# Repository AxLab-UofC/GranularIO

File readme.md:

# Granular IO
This repo contains the GUI, Arduino code, mechanical and electrical design files of the Granular IO project.

## Publication

Chi Wang, Clara Cui, Alan Pham, Justice T Andersen, Tucker Rae-Grant, and Ken Nakagaki. **Granular I/O: Enabling Bi-directional Malleable Interaction for Actuated TUIs with Magnetic Particles.** *ACM Symposium on User Interface Software and Technology (UIST 2026).* [DOI: 10.1145/3830398.3830589](https://doi.org/10.1145/3830398.3830589).

[Project Website](https://www.axlab.cs.uchicago.edu/projects/granular-io) | [Paper PDF](https://www.axlab.cs.uchicago.edu/_files/ugd/bef049_0de81f3c0d4b4951962cf3efb3ace36e.pdf) | [DOI](https://doi.org/10.1145/3830398.3830589) | [Video](https://youtu.be/jblO1pQyjmk)

## Repository structure

```text
GranularIO/
├── ArduinoCode/
│   ├── EM/                         # Firmware for the EM platform
│   └── LAPM/                       # Firmware for the LAPM platform
├── GUI/
│   └── GranularIO/                 # Graphical user interface
├── Hardware/
│   ├── EM/                         # Electromagnet array fabrication files
│   │   ├── 1_EM_Cover.stl
│   │   ├── 2_EM_Hub.stl
│   │   ├── 3_MetalDisk.step
│   │   ├── EM_Assembly.png
│   │   └── EM_Bottom.png
│   ├── LAPM/                       # LAPM fabrication files (detailed below)
│   │   ├── 1_Rail_Array.stl
│   │   ├── 2_Motor_Hub.stl
│   │   ├── 3_Supporting_Beams/
│   │   │   ├── 3_Supporting_Beam_a.stl
│   │   │   ├── 3_Supporting_Beam_b.stl
│   │   │   ├── 3_Supporting_Beam_c.stl
│   │   │   └── 3_Supporting_Beam_d.stl
│   │   ├── 4_MotherBoard_PCB/
│   │   ├── 5_MotorDriver_PCB/
│   │   ├── 6_Pin/
│   │   │   ├── 6_1_Magnet_Holder.stl
│   │   │   ├── 6_2_Screw_Connector.stl
│   │   │   └── 6_3_Encoder_Cap.stl
│   │   └── PCB Kicad Files/        # Additional KiCad-related files
│   └── Particles/                  # 3D print files for particles
├── images/                         # README illustrations
├── LICENSE
└── README.md
```

## EM hardware assembly

The EM platform uses an array of electromagnets. The annotated CAD rendering identifies the fabricated components and purchased electromagnets used in the assembly.

*Figure 1. EM assembly with numbered components. Parts 1–3 correspond to design files in `Hardware/EM/`; part 4 is a purchased electromagnet.*

| No. | File or component (inside `Hardware/EM/`) | Description | Fabrication / sourcing |
| --- | --- | --- | --- |
| **1** | `1_EM_Cover.stl` | Cover for the electromagnet array. | 3D printing |
| **2** | `2_EM_Hub.stl` | Hub that positions and supports the electromagnets within the assembly. | 3D printing |
| **3** | `3_MetalDisk.step` | Metal disk component mounted above the electromagnet units. | **Waterjet cut from sheet metal** using the supplied CAD geometry. |
| **4** | Electromagnet ([Amazon Link](https://a.co/d/0aAqXKZJ)) | Off-the-shelf electromagnet,25 x 20 mm, 12V 50N. | **Purchased online**; no fabrication file is supplied for this component. |

Additional reference images are included in `Hardware/EM/`: `EM_Assembly.png` and [`EM_Bottom.png`](Hardware/EM/EM_Bottom.png).

The STEP file for part 3 provides the metal disk geometry for waterjet-cut.

## LAPM hardware assembly

The LAPM platform contains an array of motor-driven magnetic actuator pins. The numbered callouts below correspond to the files and folders in `Hardware/LAPM/`.

*Figure 2. LAPM assembly and its six main component groups.*

### Mechanical components

| No. | File or folder (inside `Hardware/LAPM/`) | Description |
| --- | --- | --- |
| **1** | `1_Rail_Array.stl` | Rail array that guides the sliding motion of the magnets. |
| **2** | `2_Motor_Hub.stl` | Motor-mounting structure. Motors are fastened to the hub with M1.6x5mm screws; the hub also attaches to the rail array (1) and supporting beams (3). |
| **3** | `3_Supporting_Beams/` | Four separate support beams (`a`, `b`, `c`, `d`) connecting the motor hub (2) to the lower electronics assembly. |
| **4** | `4_MotherBoard_PCB/` | Fabrication files and 3D model for the motherboard PCB. |
| **5** | `5_MotorDriver_PCB/` | Fabrication files and 3D model for the motor-driver PCB, that is connected to the Mother Board with Pinheaders. |
| **6** | `6_Pin/` | 3D-printable components used in an individual actuator pin. |

### Individual actuator pin

*Figure 3. Individual motor-driven actuator pin.*

The `Hardware/LAPM/6_Pin/` folder includes:

| File | Purpose |
| --- | --- |
| `6_1_Magnet_Holder.stl` | Holds the magnet at the moving end of the actuator. |
| `6_2_Screw_Connector.stl` | Connects the screw-driven mechanism to the moving pin assembly. |
| `6_3_Encoder_Cap.stl` | Cap for the motor encoder assembly. |

[This slide](https://docs.google.com/presentation/d/1T_x9g9Pdym3wyG20I9B1YjZg6939GeQyak7WqCD--_k/edit?usp=sharing) shows how to assemble the magnet to the magnet holder and insert the heated insert.

Additionally, here is the link to the motor([Product Page](https://www.airsoftmotor.com/encoder-motor/gear-reduction-motor-with-encoder/n20-dc-gear-motor-with-3ppr-encoder.html), [supply from Taobao](https://e.tb.cn/h.jTdf8Ap64kuxkYI?tk=QmXS6ZMdcci), [Pololu Alternative](https://www.pololu.com/product/3048) and its [encoder](https://www.pololu.com/product/3081). As well as the [screws](https://www.mcmaster.com/products/screws/hex-head-screws-1~/thread-size~m3/length~40-mm/), and [magnets](https://www.kjmagnetics.com/d68-neodymium-cylinder-magnet) used in making the pin. We also recommend using [this silicone grease](https://www.amazon.com/dp/B0CSJ7NJ6Y) for lubrication, as it won't dissolve the glue used in other parts of the pin.

### PCB fabrication files

**Motherboard** — `Hardware/LAPM/4_MotherBoard_PCB/`

| File | Contents |
| --- | --- |
| `MotherBoard_Gerber.zip` | Gerber manufacturing package for the motherboard. |
| `MotherBoard_3D_Model.step` | 3D model of the PCB assembly. |
| `MotherBoard_Schematic.pdf` | Circuit schematic. |
| `MotherBoard_PCB_F.pdf` | Front-side PCB drawing. |
| `MotherBoard_PCB_B.pdf` | Back-side PCB drawing. |
| `readme.md` | Additional motherboard-specific documentation. |

**Motor-driver board** — `Hardware/LAPM/5_MotorDriver_PCB/`

| File | Contents |
| --- | --- |
| `MotorDriverGerber.zip` | Gerber manufacturing package for the motor-driver board. |
| `MotorDriver_3D_Model.step` | 3D model of the PCB assembly. |
| `MotorDriver_Schematic.pdf` | Circuit schematic. |
| `MotorDriver_PCB_F.pdf` | Front-side PCB drawing. |
| `MotorDriver_PCB_B.pdf` | Back-side PCB drawing. |
| `MotorDriver_BOM.csv` | Component bill of materials. |
| `MotorDriver_pos.csv` | Component placement/position data. |

A separate `Hardware/LAPM/PCB Kicad Files/` folder is also included for additional PCB design files. See the files in that folder for their supported formats and revisions.

### Complete assembly

*Figure 4. Assembled LAPM motor array, support frame, and electronics.*

## Particles

| File | Purpose |
| --- | --- |
| `Sphere_5mm_mini.3mf` | Fabrication File for using 3D printers to make the particles. |
| `Sphere_5mm_support_test.3mf` | Optional fabrication file to test the printer support setting, this is useful when printing with special filaments. |

Here is a [guide](https://docs.google.com/document/d/1k1LIMI7lGGnSAPhkvcHD0EtzRTSeqdstu-cQaYbHAh0/edit?usp=sharing) to make the particles.

## Fabrication notes

- The `.stl` files are intended for 3D-printing the mechanical components. The EM `3_MetalDisk.step` is for waterjet cutting metal sheet; the PCB `.step` files provide 3D board models.
- Gerber archives are intended for PCB fabrication; schematic PDFs and front/back drawings are provided for reference. For the motor-driver PCB, a BOM and placement file are also included.
- Motors, magnets, electromagnets, screws, and other off-the-shelf components must be sourced separately; they are not included in the printable STL files.
- The files are provided as design and fabrication resources, **not** as a complete tested assembly guide. Check dimensions, interfaces, manufacturing requirements, and file revisions before ordering parts.

## Publication

Chi Wang, Clara Cui, Alan Pham, Justice T Andersen, Tucker Rae-Grant, and Ken Nakagaki. **Granular I/O: Enabling Bi-directional Malleable Interaction for Actuated TUIs with Magnetic Particles.** *ACM Symposium on User Interface Software and Technology (UIST 2026).* [DOI: 10.1145/3830398.3830589](https://doi.org/10.1145/3830398.3830589).

## License

See the [LICENSE](LICENSE) file for usage and redistribution terms.

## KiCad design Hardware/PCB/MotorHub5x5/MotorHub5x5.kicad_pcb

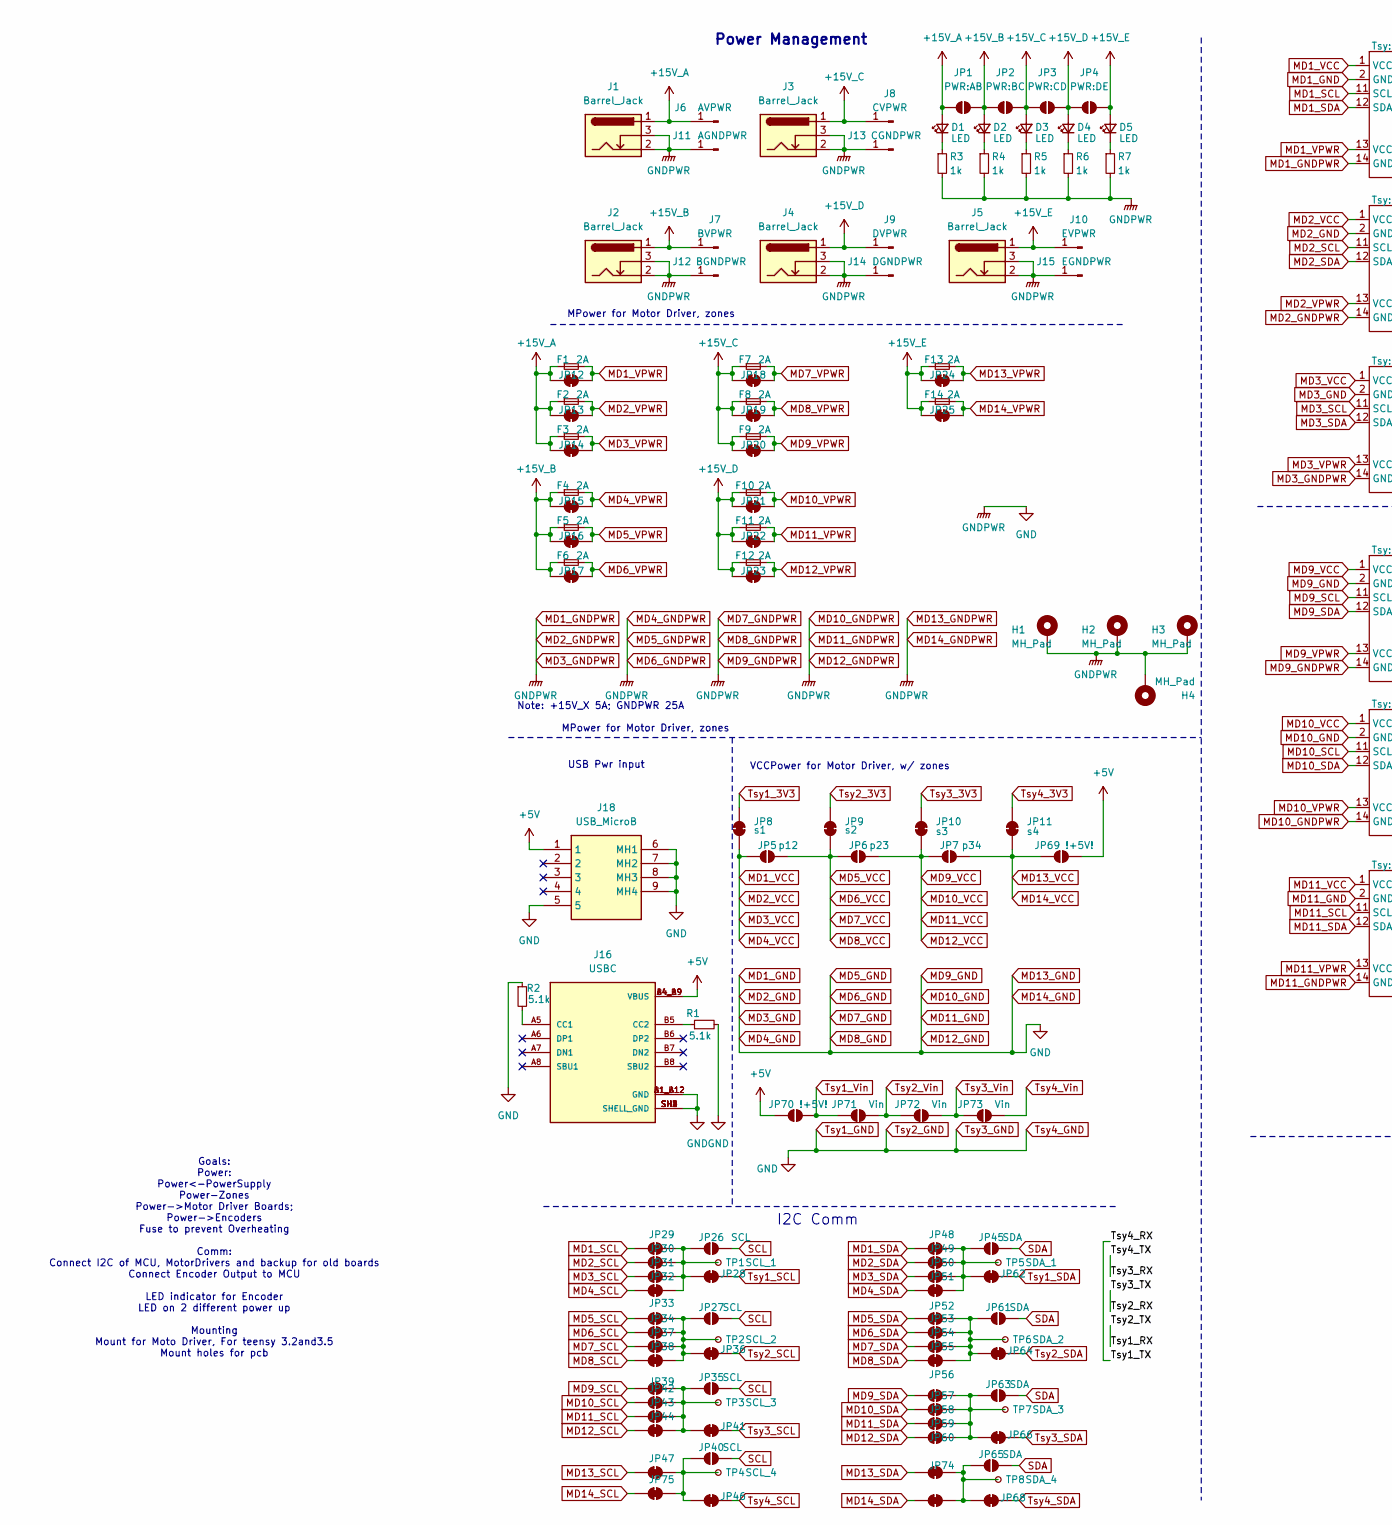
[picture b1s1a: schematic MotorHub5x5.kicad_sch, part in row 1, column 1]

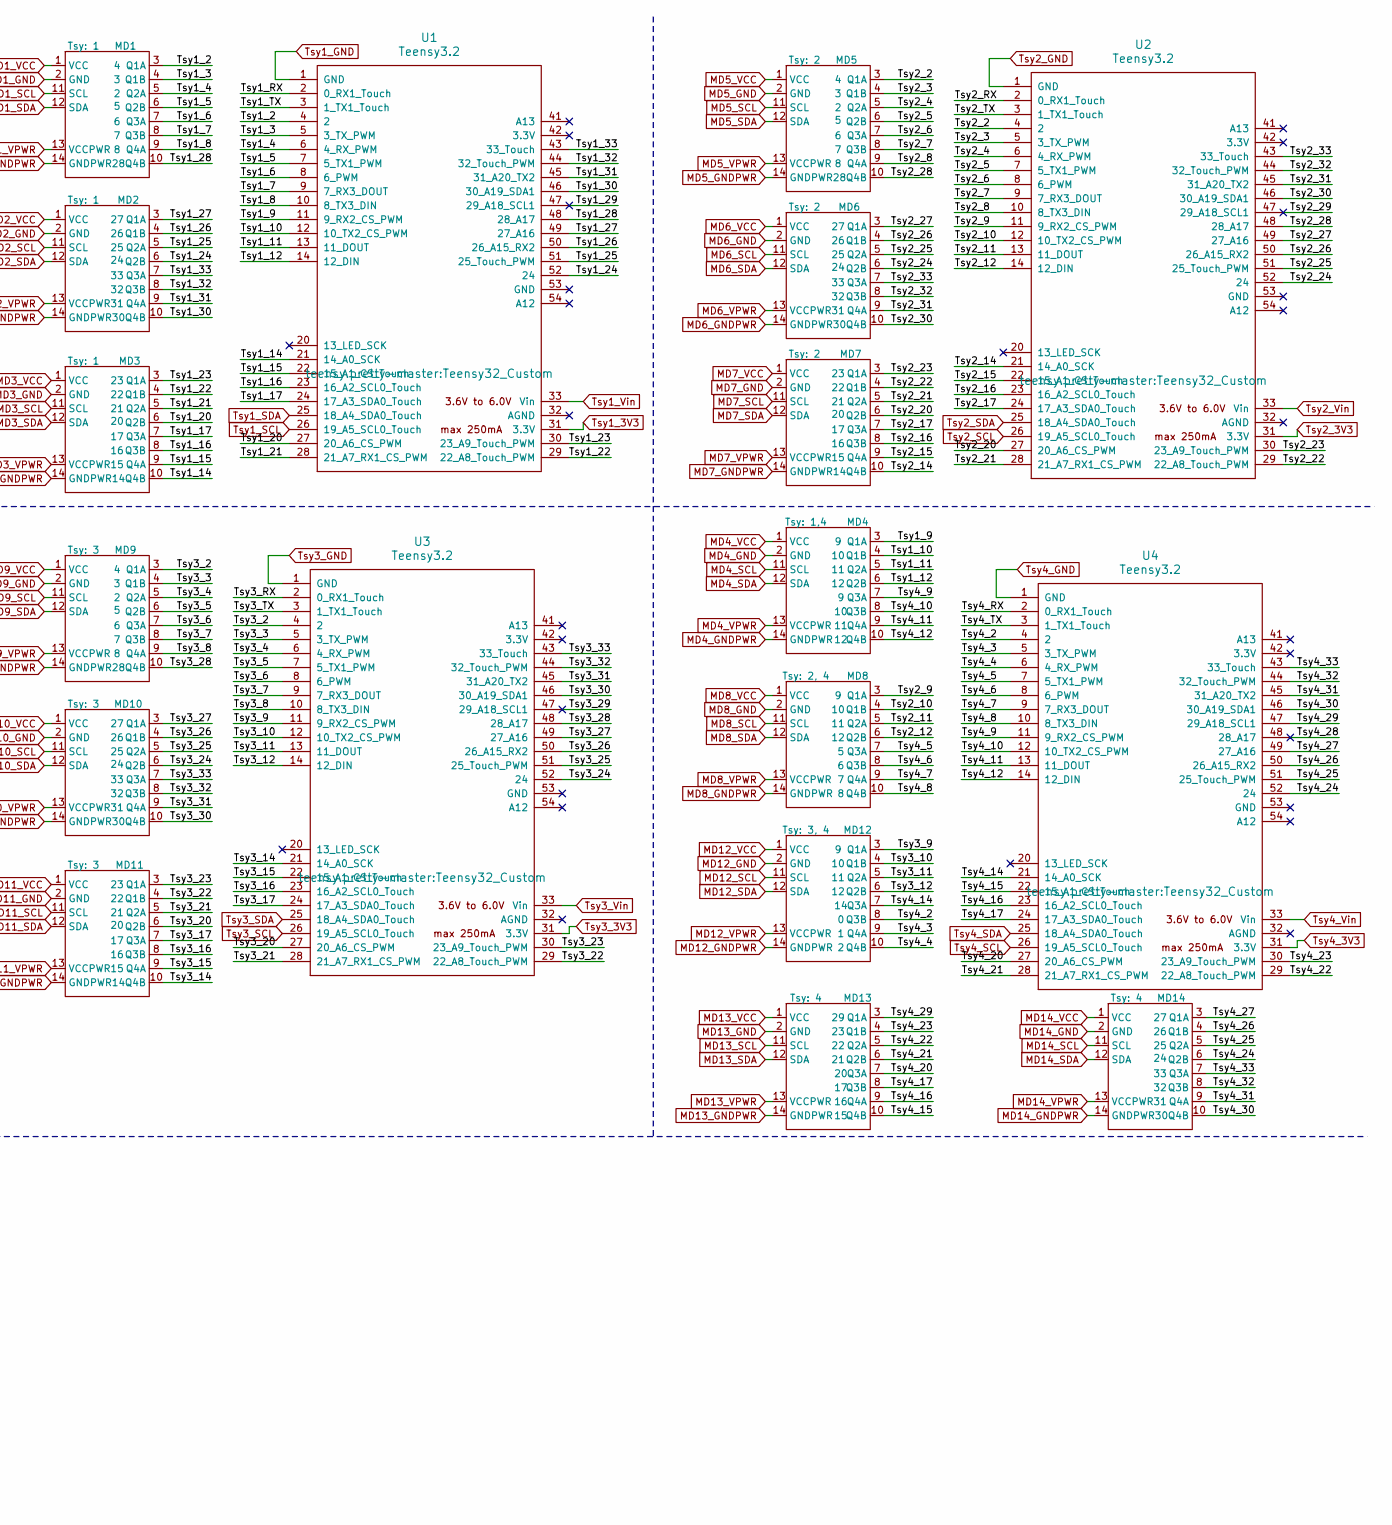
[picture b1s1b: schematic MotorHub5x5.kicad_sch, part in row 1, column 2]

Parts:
D1, D2, D3, D4, D5: LED; LED_0603_1608Metric_Pad1.05x0.95mm_HandSolder
F1, F2, F3, F4, F5, F6, F7, F8, F9, F10, F11, F12, F13, F14: 2A; Fuse_2920_7451Metric_Pad2.10x5.45mm_HandSolder_custom
H1, H2, H3: MH_Pad; MountingHole_3.2mm_M3_Pad_Via
H4: MH_Pad; MountingHole_2.2mm_M2_Pad
J1, J2, J3, J4, J5: Barrel_Jack; DC_Barral_JackCUI_PJ-002B
J6: AVPWR; PinHeader_1x01_P2.54mm_Vertical
J7: BVPWR; PinHeader_1x01_P2.54mm_Vertical
J8: CVPWR; PinHeader_1x01_P2.54mm_Vertical
J9: DVPWR; PinHeader_1x01_P2.54mm_Vertical
J10: EVPWR; PinHeader_1x01_P2.54mm_Vertical
J11: AGNDPWR; PinHeader_1x01_P2.54mm_Vertical
J12: BGNDPWR; PinHeader_1x01_P2.54mm_Vertical
J13: CGNDPWR; PinHeader_1x01_P2.54mm_Vertical
J14: DGNDPWR; PinHeader_1x01_P2.54mm_Vertical
J15: EGNDPWR; PinHeader_1x01_P2.54mm_Vertical
J16: USBC; GCT_USB4105-GF-A
J18: USB_MicroB; MCRBSRASMTCS5ANFTR; Mouser Part Number 737-RBSRASMTCS5ANFTR
JP1: PWR:AB; SolderJumper-2_P3mm_Open_RectPad
JP2: PWR:BC; SolderJumper-2_P3mm_Open_RectPad
JP3: PWR:CD; SolderJumper-2_P3mm_Open_RectPad
JP4: PWR:DE; SolderJumper-2_P3mm_Open_RectPad
JP5: p12; SolderJumper-2_Open_RoundedPad
JP6: p23; SolderJumper-2_Open_RoundedPad
JP7: p34; SolderJumper-2_Open_RoundedPad
JP8: s1; SolderJumper-2_Bridged_RoundedPad
JP9: s2; SolderJumper-2_Bridged_RoundedPad
JP10: s3; SolderJumper-2_Bridged_RoundedPad
JP11: s4; SolderJumper-2_Bridged_RoundedPad
JP12: DM1; SolderJumper-2_P1.3mm_Bridged2Bar_RoundedPad1.0x1.5mm
JP13: DM2; SolderJumper-2_P1.3mm_Bridged2Bar_RoundedPad1.0x1.5mm
JP14: DM3; SolderJumper-2_P1.3mm_Bridged2Bar_RoundedPad1.0x1.5mm
JP15: DM4; SolderJumper-2_P1.3mm_Bridged2Bar_RoundedPad1.0x1.5mm
JP16: DM5; SolderJumper-2_P1.3mm_Bridged2Bar_RoundedPad1.0x1.5mm
JP17: DM6; SolderJumper-2_P1.3mm_Bridged2Bar_RoundedPad1.0x1.5mm
JP18: DM7; SolderJumper-2_P1.3mm_Bridged2Bar_RoundedPad1.0x1.5mm
JP19: DM8; SolderJumper-2_P1.3mm_Bridged2Bar_RoundedPad1.0x1.5mm
JP20: DM9; SolderJumper-2_P1.3mm_Bridged2Bar_RoundedPad1.0x1.5mm
JP21: DM10; SolderJumper-2_P1.3mm_Bridged2Bar_RoundedPad1.0x1.5mm
JP22: DM11; SolderJumper-2_P1.3mm_Bridged2Bar_RoundedPad1.0x1.5mm
JP23: DM12; SolderJumper-2_P1.3mm_Bridged2Bar_RoundedPad1.0x1.5mm
JP24, JP25: DM13; SolderJumper-2_P1.3mm_Bridged2Bar_RoundedPad1.0x1.5mm
JP26, JP27, JP35, JP40: SCL; SolderJumper-2_Open_RoundedPad
JP28, JP29, JP30, JP31, JP32, JP33, JP34, JP36, JP37, JP38, JP39, JP41, JP42, JP43, JP44, JP46, JP47, JP48, JP49, JP50, JP51, JP52, JP53, JP54, JP55, JP56, JP57, JP58, JP59, JP60, JP62, JP64, JP66, JP68, JP74, JP75: SolderJumper_2_Bridged; SolderJumper-2_Bridged_RoundedPad
JP45, JP61, JP63, JP65: SDA; SolderJumper-2_Open_RoundedPad
JP69, JP70: !+5V!; SolderJumper-2_Open_RoundedPad
JP71, JP72, JP73: Vin; SolderJumper-2_Open_RoundedPad
MD1, MD2, MD3, MD4, MD5, MD6, MD7, MD8, MD9, MD10, MD11, MD12, MD13, MD14: MotorDriverConn
R1, R2: 5.1k; R_0603_1608Metric_Pad0.98x0.95mm_HandSolder
R3, R4, R5, R6, R7: 1k; R_0603_1608Metric_Pad0.98x0.95mm_HandSolder
TP1: SCL_1; PinSocket_1x01_P2.54mm_Vertical
TP2: SCL_2; PinSocket_1x01_P2.54mm_Vertical
TP3: SCL_3; PinSocket_1x01_P2.54mm_Vertical
TP4: SCL_4; PinSocket_1x01_P2.54mm_Vertical
TP5: SDA_1; PinSocket_1x01_P2.54mm_Vertical
TP6: SDA_2; PinSocket_1x01_P2.54mm_Vertical
TP7: SDA_3; PinSocket_1x01_P2.54mm_Vertical
TP8: SDA_4; PinSocket_1x01_P2.54mm_Vertical
U1, U2, U3, U4: Teensy3.2; Teensy32_Custom

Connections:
+5V: J16.A4_B9 (VBUS), J16.B4_A9 (VBUS), J18.1, JP69.2 (B), JP70.1 (A)
+15V_A: D1.2 (A), F1.1, F2.1, F3.1, J1.1, J6.1, JP1.1 (A), JP12.1 (A), JP13.1 (A), JP14.1 (A)
+15V_B: D2.2 (A), F4.1, F5.1, F6.1, J2.1, J7.1, JP1.2 (B), JP2.1 (A), JP15.1 (A), JP16.1 (A), JP17.1 (A)
+15V_C: D3.2 (A), F7.1, F8.1, F9.1, J3.1, J8.1, JP2.2 (B), JP3.1 (A), JP18.1 (A), JP19.1 (A), JP20.1 (A)
+15V_D: D4.2 (A), F10.1, F11.1, F12.1, J4.1, J9.1, JP3.2 (B), JP4.1 (A), JP21.1 (A), JP22.1 (A), JP23.1 (A)
+15V_E: D5.2 (A), F13.1, F14.1, J5.1, J10.1, JP4.2 (B), JP24.1 (A), JP25.1 (A)
/Tsy1_2: MD1.3 (Q1A), U1.4 (2)
/Tsy1_3: MD1.4 (Q1B), U1.5 (3_TX_PWM)
/Tsy1_4: MD1.5 (Q2A), U1.6 (4_RX_PWM)
/Tsy1_5: MD1.6 (Q2B), U1.7 (5_TX1_PWM)
/Tsy1_6: MD1.7 (Q3A), U1.8 (6_PWM)
/Tsy1_7: MD1.8 (Q3B), U1.9 (7_RX3_DOUT)
/Tsy1_8: MD1.9 (Q4A), U1.10 (8_TX3_DIN)
/Tsy1_9: MD4.3 (Q1A), U1.11 (9_RX2_CS_PWM)
/Tsy1_10: MD4.4 (Q1B), U1.12 (10_TX2_CS_PWM)
/Tsy1_11: MD4.5 (Q2A), U1.13 (11_DOUT)
/Tsy1_12: MD4.6 (Q2B), U1.14 (12_DIN)
/Tsy1_14: MD3.10 (Q4B), U1.21 (14_A0_SCK)
/Tsy1_15: MD3.9 (Q4A), U1.22 (15_A1_CS_Touch)
/Tsy1_16: MD3.8 (Q3B), U1.23 (16_A2_SCL0_Touch)
/Tsy1_17: MD3.7 (Q3A), U1.24 (17_A3_SDA0_Touch)
/Tsy1_20: MD3.6 (Q2B), U1.27 (20_A6_CS_PWM)
/Tsy1_21: MD3.5 (Q2A), U1.28 (21_A7_RX1_CS_PWM)
/Tsy1_22: MD3.4 (Q1B), U1.29 (22_A8_Touch_PWM)
/Tsy1_23: MD3.3 (Q1A), U1.30 (23_A9_Touch_PWM)
/Tsy1_24: MD2.6 (Q2B), U1.52 (24)
/Tsy1_25: MD2.5 (Q2A), U1.51 (25_Touch_PWM)
/Tsy1_26: MD2.4 (Q1B), U1.50 (26_A15_RX2)
/Tsy1_27: MD2.3 (Q1A), U1.49 (27_A16)
/Tsy1_28: MD1.10 (Q4B), U1.48 (28_A17)
/Tsy1_29: U1.47 (29_A18_SCL1)
/Tsy1_30: MD2.10 (Q4B), U1.46 (30_A19_SDA1)
/Tsy1_31: MD2.9 (Q4A), U1.45 (31_A20_TX2)
/Tsy1_32: MD2.8 (Q3B), U1.44 (32_Touch_PWM)
/Tsy1_33: MD2.7 (Q3A), U1.43 (33_Touch)
/Tsy1_RX: U1.2 (0_RX1_Touch), U2.3 (1_TX1_Touch)
/Tsy1_TX: U1.3 (1_TX1_Touch), U4.2 (0_RX1_Touch)
/Tsy2_2: MD5.3 (Q1A), U2.4 (2)
/Tsy2_3: MD5.4 (Q1B), U2.5 (3_TX_PWM)
/Tsy2_4: MD5.5 (Q2A), U2.6 (4_RX_PWM)
/Tsy2_5: MD5.6 (Q2B), U2.7 (5_TX1_PWM)
/Tsy2_6: MD5.7 (Q3A), U2.8 (6_PWM)
/Tsy2_7: MD5.8 (Q3B), U2.9 (7_RX3_DOUT)
/Tsy2_8: MD5.9 (Q4A), U2.10 (8_TX3_DIN)
/Tsy2_9: MD8.3 (Q1A), U2.11 (9_RX2_CS_PWM)
/Tsy2_10: MD8.4 (Q1B), U2.12 (10_TX2_CS_PWM)
/Tsy2_11: MD8.5 (Q2A), U2.13 (11_DOUT)
/Tsy2_12: MD8.6 (Q2B), U2.14 (12_DIN)
/Tsy2_14: MD7.10 (Q4B), U2.21 (14_A0_SCK)
/Tsy2_15: MD7.9 (Q4A), U2.22 (15_A1_CS_Touch)
/Tsy2_16: MD7.8 (Q3B), U2.23 (16_A2_SCL0_Touch)
/Tsy2_17: MD7.7 (Q3A), U2.24 (17_A3_SDA0_Touch)
/Tsy2_20: MD7.6 (Q2B), U2.27 (20_A6_CS_PWM)
/Tsy2_21: MD7.5 (Q2A), U2.28 (21_A7_RX1_CS_PWM)
/Tsy2_22: MD7.4 (Q1B), U2.29 (22_A8_Touch_PWM)
/Tsy2_23: MD7.3 (Q1A), U2.30 (23_A9_Touch_PWM)
/Tsy2_24: MD6.6 (Q2B), U2.52 (24)
/Tsy2_25: MD6.5 (Q2A), U2.51 (25_Touch_PWM)
/Tsy2_26: MD6.4 (Q1B), U2.50 (26_A15_RX2)
/Tsy2_27: MD6.3 (Q1A), U2.49 (27_A16)
/Tsy2_28: MD5.10 (Q4B), U2.48 (28_A17)
/Tsy2_29: U2.47 (29_A18_SCL1)
/Tsy2_30: MD6.10 (Q4B), U2.46 (30_A19_SDA1)
/Tsy2_31: MD6.9 (Q4A), U2.45 (31_A20_TX2)
/Tsy2_32: MD6.8 (Q3B), U2.44 (32_Touch_PWM)
/Tsy2_33: MD6.7 (Q3A), U2.43 (33_Touch)
/Tsy2_RX: U2.2 (0_RX1_Touch), U3.3 (1_TX1_Touch)
/Tsy3_2: MD9.3 (Q1A), U3.4 (2)
/Tsy3_3: MD9.4 (Q1B), U3.5 (3_TX_PWM)
/Tsy3_4: MD9.5 (Q2A), U3.6 (4_RX_PWM)
/Tsy3_5: MD9.6 (Q2B), U3.7 (5_TX1_PWM)
/Tsy3_6: MD9.7 (Q3A), U3.8 (6_PWM)
/Tsy3_7: MD9.8 (Q3B), U3.9 (7_RX3_DOUT)
/Tsy3_8: MD9.9 (Q4A), U3.10 (8_TX3_DIN)
/Tsy3_9: MD12.3 (Q1A), U3.11 (9_RX2_CS_PWM)
/Tsy3_10: MD12.4 (Q1B), U3.12 (10_TX2_CS_PWM)
/Tsy3_11: MD12.5 (Q2A), U3.13 (11_DOUT)
/Tsy3_12: MD12.6 (Q2B), U3.14 (12_DIN)
/Tsy3_14: MD11.10 (Q4B), U3.21 (14_A0_SCK)
/Tsy3_15: MD11.9 (Q4A), U3.22 (15_A1_CS_Touch)
/Tsy3_16: MD11.8 (Q3B), U3.23 (16_A2_SCL0_Touch)
/Tsy3_17: MD11.7 (Q3A), U3.24 (17_A3_SDA0_Touch)
/Tsy3_20: MD11.6 (Q2B), U3.27 (20_A6_CS_PWM)
/Tsy3_21: MD11.5 (Q2A), U3.28 (21_A7_RX1_CS_PWM)
/Tsy3_22: MD11.4 (Q1B), U3.29 (22_A8_Touch_PWM)
/Tsy3_23: MD11.3 (Q1A), U3.30 (23_A9_Touch_PWM)
/Tsy3_24: MD10.6 (Q2B), U3.52 (24)
/Tsy3_25: MD10.5 (Q2A), U3.51 (25_Touch_PWM)
/Tsy3_26: MD10.4 (Q1B), U3.50 (26_A15_RX2)
/Tsy3_27: MD10.3 (Q1A), U3.49 (27_A16)
/Tsy3_28: MD9.10 (Q4B), U3.48 (28_A17)
/Tsy3_29: U3.47 (29_A18_SCL1)
/Tsy3_30: MD10.10 (Q4B), U3.46 (30_A19_SDA1)
/Tsy3_31: MD10.9 (Q4A), U3.45 (31_A20_TX2)
/Tsy3_32: MD10.8 (Q3B), U3.44 (32_Touch_PWM)
/Tsy3_33: MD10.7 (Q3A), U3.43 (33_Touch)
/Tsy3_RX: U3.2 (0_RX1_Touch), U4.3 (1_TX1_Touch)
/Tsy4_2: MD12.8 (Q3B), U4.4 (2)
/Tsy4_3: MD12.9 (Q4A), U4.5 (3_TX_PWM)
/Tsy4_4: MD12.10 (Q4B), U4.6 (4_RX_PWM)
/Tsy4_5: MD8.7 (Q3A), U4.7 (5_TX1_PWM)
/Tsy4_6: MD8.8 (Q3B), U4.8 (6_PWM)
/Tsy4_7: MD8.9 (Q4A), U4.9 (7_RX3_DOUT)
/Tsy4_8: MD8.10 (Q4B), U4.10 (8_TX3_DIN)
/Tsy4_9: MD4.7 (Q3A), U4.11 (9_RX2_CS_PWM)
/Tsy4_10: MD4.8 (Q3B), U4.12 (10_TX2_CS_PWM)
/Tsy4_11: MD4.9 (Q4A), U4.13 (11_DOUT)
/Tsy4_12: MD4.10 (Q4B), U4.14 (12_DIN)
/Tsy4_14: MD12.7 (Q3A), U4.21 (14_A0_SCK)
/Tsy4_15: MD13.10 (Q4B), U4.22 (15_A1_CS_Touch)
/Tsy4_16: MD13.9 (Q4A), U4.23 (16_A2_SCL0_Touch)
/Tsy4_17: MD13.8 (Q3B), U4.24 (17_A3_SDA0_Touch)
/Tsy4_20: MD13.7 (Q3A), U4.27 (20_A6_CS_PWM)
/Tsy4_21: MD13.6 (Q2B), U4.28 (21_A7_RX1_CS_PWM)
/Tsy4_22: MD13.5 (Q2A), U4.29 (22_A8_Touch_PWM)
/Tsy4_23: MD13.4 (Q1B), U4.30 (23_A9_Touch_PWM)
/Tsy4_24: MD14.6 (Q2B), U4.52 (24)
/Tsy4_25: MD14.5 (Q2A), U4.51 (25_Touch_PWM)
/Tsy4_26: MD14.4 (Q1B), U4.50 (26_A15_RX2)
/Tsy4_27: MD14.3 (Q1A), U4.49 (27_A16)
/Tsy4_28: U4.48 (28_A17)
/Tsy4_29: MD13.3 (Q1A), U4.47 (29_A18_SCL1)
/Tsy4_30: MD14.10 (Q4B), U4.46 (30_A19_SDA1)
/Tsy4_31: MD14.9 (Q4A), U4.45 (31_A20_TX2)
/Tsy4_32: MD14.8 (Q3B), U4.44 (32_Touch_PWM)
/Tsy4_33: MD14.7 (Q3A), U4.43 (33_Touch)
MD1_SCL: JP29.2 (B), MD1.11 (SCL)
MD1_SDA: JP48.2 (B), MD1.12 (SDA)
MD1_VCC: JP5.1 (A), JP8.1 (A), MD1.1 (VCC), MD2.1 (VCC), MD3.1 (VCC), MD4.1 (VCC)
MD1_VPWR: F1.2, JP12.2 (B), MD1.13 (VCCPWR)
MD2_SCL: JP30.2 (B), MD2.11 (SCL)
MD2_SDA: JP49.2 (B), MD2.12 (SDA)
MD2_VPWR: F2.2, JP13.2 (B), MD2.13 (VCCPWR)
MD3_SCL: JP31.2 (B), MD3.11 (SCL)
MD3_SDA: JP50.2 (B), MD3.12 (SDA)
MD3_VPWR: F3.2, JP14.2 (B), MD3.13 (VCCPWR)
MD4_SCL: JP32.2 (B), MD4.11 (SCL)
MD4_SDA: JP51.2 (B), MD4.12 (SDA)
MD4_VPWR: F4.2, JP15.2 (B), MD4.13 (VCCPWR)
MD5_SCL: JP33.2 (B), MD5.11 (SCL)
MD5_SDA: JP52.2 (B), MD5.12 (SDA)
MD5_VCC: JP5.2 (B), JP6.1 (A), JP9.1 (A), MD5.1 (VCC), MD6.1 (VCC), MD7.1 (VCC), MD8.1 (VCC)
MD5_VPWR: F5.2, JP16.2 (B), MD5.13 (VCCPWR)
MD6_SCL: JP34.2 (B), MD6.11 (SCL)
MD6_SDA: JP53.2 (B), MD6.12 (SDA)
MD6_VPWR: F6.2, JP17.2 (B), MD6.13 (VCCPWR)
MD7_SCL: JP37.2 (B), MD7.11 (SCL)
MD7_SDA: JP54.2 (B), MD7.12 (SDA)
MD7_VPWR: F7.2, JP18.2 (B), MD7.13 (VCCPWR)
MD8_SCL: JP38.2 (B), MD8.11 (SCL)
MD8_SDA: JP55.2 (B), MD8.12 (SDA)
MD8_VPWR: F8.2, JP19.2 (B), MD8.13 (VCCPWR)
MD9_SCL: JP39.2 (B), MD9.11 (SCL)
MD9_SDA: JP56.2 (B), MD9.12 (SDA)
MD9_VPWR: F9.2, JP20.2 (B), MD9.13 (VCCPWR)
MD10_GND: H1.1, H2.1, H3.1, H4.1, J1.2, J1.3, J2.2, J2.3, J3.2, J3.3, J4.2, J4.3, J5.2, J5.3, J11.1, J12.1, J13.1, J14.1, J15.1, J16.A1_B12 (GND), J16.B1_A12 (GND), J16.SH1 (SHELL_GND), J16.SH2 (SHELL_GND), J16.SH3 (SHELL_GND), J16.SH4 (SHELL_GND), J18.5, J18.6 (MH1), J18.7 (MH2), J18.8 (MH3), J18.9 (MH4), MD1.2 (GND), MD1.14 (GNDPWR), MD2.2 (GND), MD2.14 (GNDPWR), MD3.2 (GND), MD3.14 (GNDPWR), MD4.2 (GND), MD4.14 (GNDPWR), MD5.2 (GND), MD5.14 (GNDPWR), MD6.2 (GND), MD6.14 (GNDPWR), MD7.2 (GND), MD7.14 (GNDPWR), MD8.2 (GND), MD8.14 (GNDPWR), MD9.2 (GND), MD9.14 (GNDPWR), MD10.2 (GND), MD10.14 (GNDPWR), MD11.2 (GND), MD11.14 (GNDPWR), MD12.2 (GND), MD12.14 (GNDPWR), MD13.2 (GND), MD13.14 (GNDPWR), MD14.2 (GND), MD14.14 (GNDPWR), R1.2, R2.1, R3.2, R4.2, R5.2, R6.2, R7.2, U1.1 (GND), U2.1 (GND), U3.1 (GND), U4.1 (GND)
MD10_SCL: JP42.2 (B), MD10.11 (SCL)
MD10_SDA: JP57.2 (B), MD10.12 (SDA)
MD10_VCC: JP6.2 (B), JP7.1 (A), JP10.1 (A), MD9.1 (VCC), MD10.1 (VCC), MD11.1 (VCC), MD12.1 (VCC)
MD10_VPWR: F10.2, JP21.2 (B), MD10.13 (VCCPWR)
MD11_SCL: JP43.2 (B), MD11.11 (SCL)
MD11_SDA: JP58.2 (B), MD11.12 (SDA)
MD11_VPWR: F11.2, JP22.2 (B), MD11.13 (VCCPWR)
MD12_SCL: JP44.2 (B), MD12.11 (SCL)
MD12_SDA: JP59.2 (B), MD12.12 (SDA)
MD12_VPWR: F12.2, JP23.2 (B), MD12.13 (VCCPWR)
MD13_SCL: JP47.2 (B), MD13.11 (SCL)
MD13_SDA: JP60.2 (B), MD13.12 (SDA)
MD13_VCC: JP7.2 (B), JP11.1 (A), JP69.1 (A), MD13.1 (VCC), MD14.1 (VCC)
MD13_VPWR: F13.2, JP24.2 (B), MD13.13 (VCCPWR)
MD14_SCL: JP75.2 (B), MD14.11 (SCL)
MD14_SDA: JP74.2 (B), MD14.12 (SDA)
MD14_VPWR: F14.2, JP25.2 (B), MD14.13 (VCCPWR)
unnamed: D1.1 (K), R3.1
unnamed: D2.1 (K), R4.1
unnamed: D3.1 (K), R5.1
unnamed: D4.1 (K), R6.1
unnamed: D5.1 (K), R7.1
unnamed: J16.A5 (CC1), R2.2
unnamed: J16.B5 (CC2), R1.1
unnamed: JP26.1 (A), JP28.2 (B), JP29.1 (A), JP30.1 (A), JP31.1 (A), JP32.1 (A), TP1.1
unnamed: JP27.1 (A), JP33.1 (A), JP34.1 (A), JP36.2 (B), JP37.1 (A), JP38.1 (A), TP2.1
unnamed: JP35.1 (A), JP39.1 (A), JP41.2 (B), JP42.1 (A), JP43.1 (A), JP44.1 (A), TP3.1
unnamed: JP40.1 (A), JP46.2 (B), JP47.1 (A), JP75.1 (A), TP4.1
unnamed: JP45.1 (A), JP48.1 (A), JP49.1 (A), JP50.1 (A), JP51.1 (A), JP62.2 (B), TP5.1
unnamed: JP52.1 (A), JP53.1 (A), JP54.1 (A), JP55.1 (A), JP61.1 (A), JP64.2 (B), TP6.1
unnamed: JP56.1 (A), JP57.1 (A), JP58.1 (A), JP59.1 (A), JP63.1 (A), JP66.2 (B), TP7.1
unnamed: JP60.1 (A), JP65.1 (A), JP68.2 (B), JP74.1 (A), TP8.1
SCL: JP26.2 (B), JP27.2 (B), JP35.2 (B), JP40.2 (B)
SDA: JP45.2 (B), JP61.2 (B), JP63.2 (B), JP65.2 (B)
Tsy1_3V3: JP8.2 (B), U1.31 (3.3V)
Tsy1_SCL: JP28.1 (A), U1.26 (19_A5_SCL0_Touch)
Tsy1_SDA: JP62.1 (A), U1.25 (18_A4_SDA0_Touch)
Tsy1_Vin: JP70.2 (B), JP71.1 (A), U1.33 (Vin)
Tsy2_3V3: JP9.2 (B), U2.31 (3.3V)
Tsy2_SCL: JP36.1 (A), U2.26 (19_A5_SCL0_Touch)
Tsy2_SDA: JP64.1 (A), U2.25 (18_A4_SDA0_Touch)
Tsy2_Vin: JP71.2 (B), JP72.1 (A), U2.33 (Vin)
Tsy3_3V3: JP10.2 (B), U3.31 (3.3V)
Tsy3_SCL: JP41.1 (A), U3.26 (19_A5_SCL0_Touch)
Tsy3_SDA: JP66.1 (A), U3.25 (18_A4_SDA0_Touch)
Tsy3_Vin: JP72.2 (B), JP73.1 (A), U3.33 (Vin)
Tsy4_3V3: JP11.2 (B), U4.31 (3.3V)
Tsy4_SCL: JP46.1 (A), U4.26 (19_A5_SCL0_Touch)
Tsy4_SDA: JP68.1 (A), U4.25 (18_A4_SDA0_Touch)
Tsy4_Vin: JP73.2 (B), U4.33 (Vin)

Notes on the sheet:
MPower for Motor Driver, zones
Power Management
USB Pwr input
VCCPower for Motor Driver, w/ zones
Note: +15V_X 5A; GNDPWR 25A
Goals: Power: Power<-PowerSupply Power-Zones Power->Motor Driver Boards; Power->Encoders Fuse to prevent Overheating Comm: Connect I2C of MCU, MotorDrivers and backup for old boards Connect Encoder Output to MCU LED indicator for Encoder LED on 2 different power up Mounting Mount for Moto Driver, F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
I2C Comm

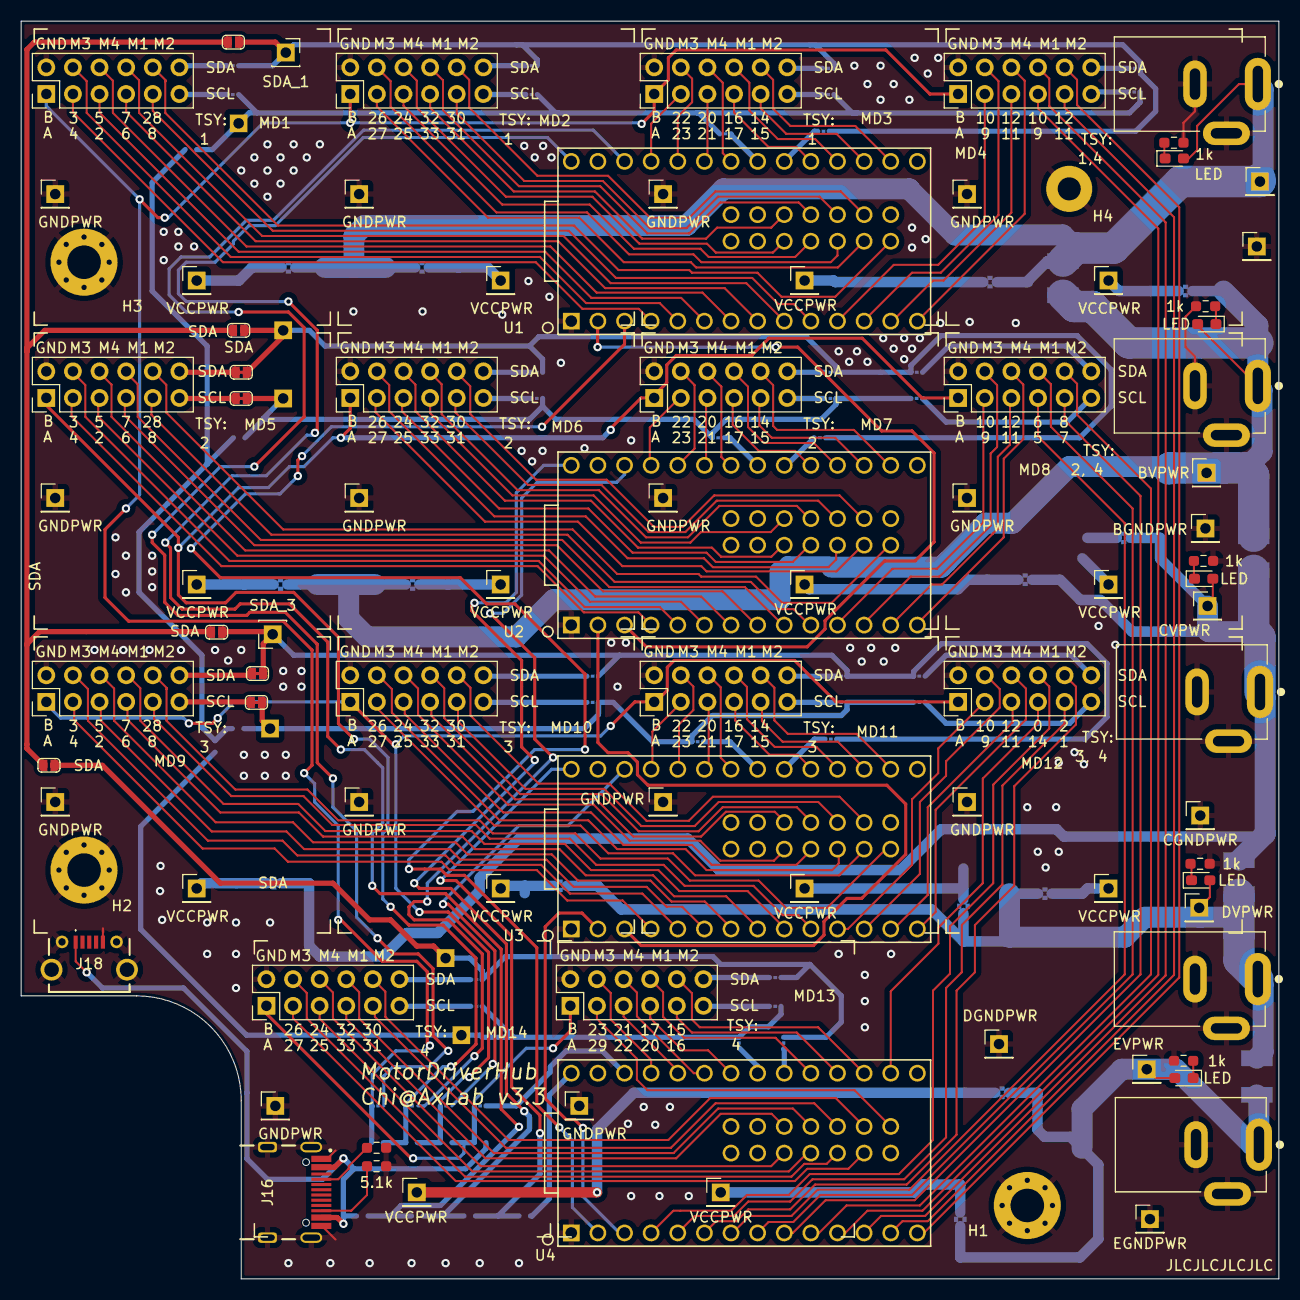
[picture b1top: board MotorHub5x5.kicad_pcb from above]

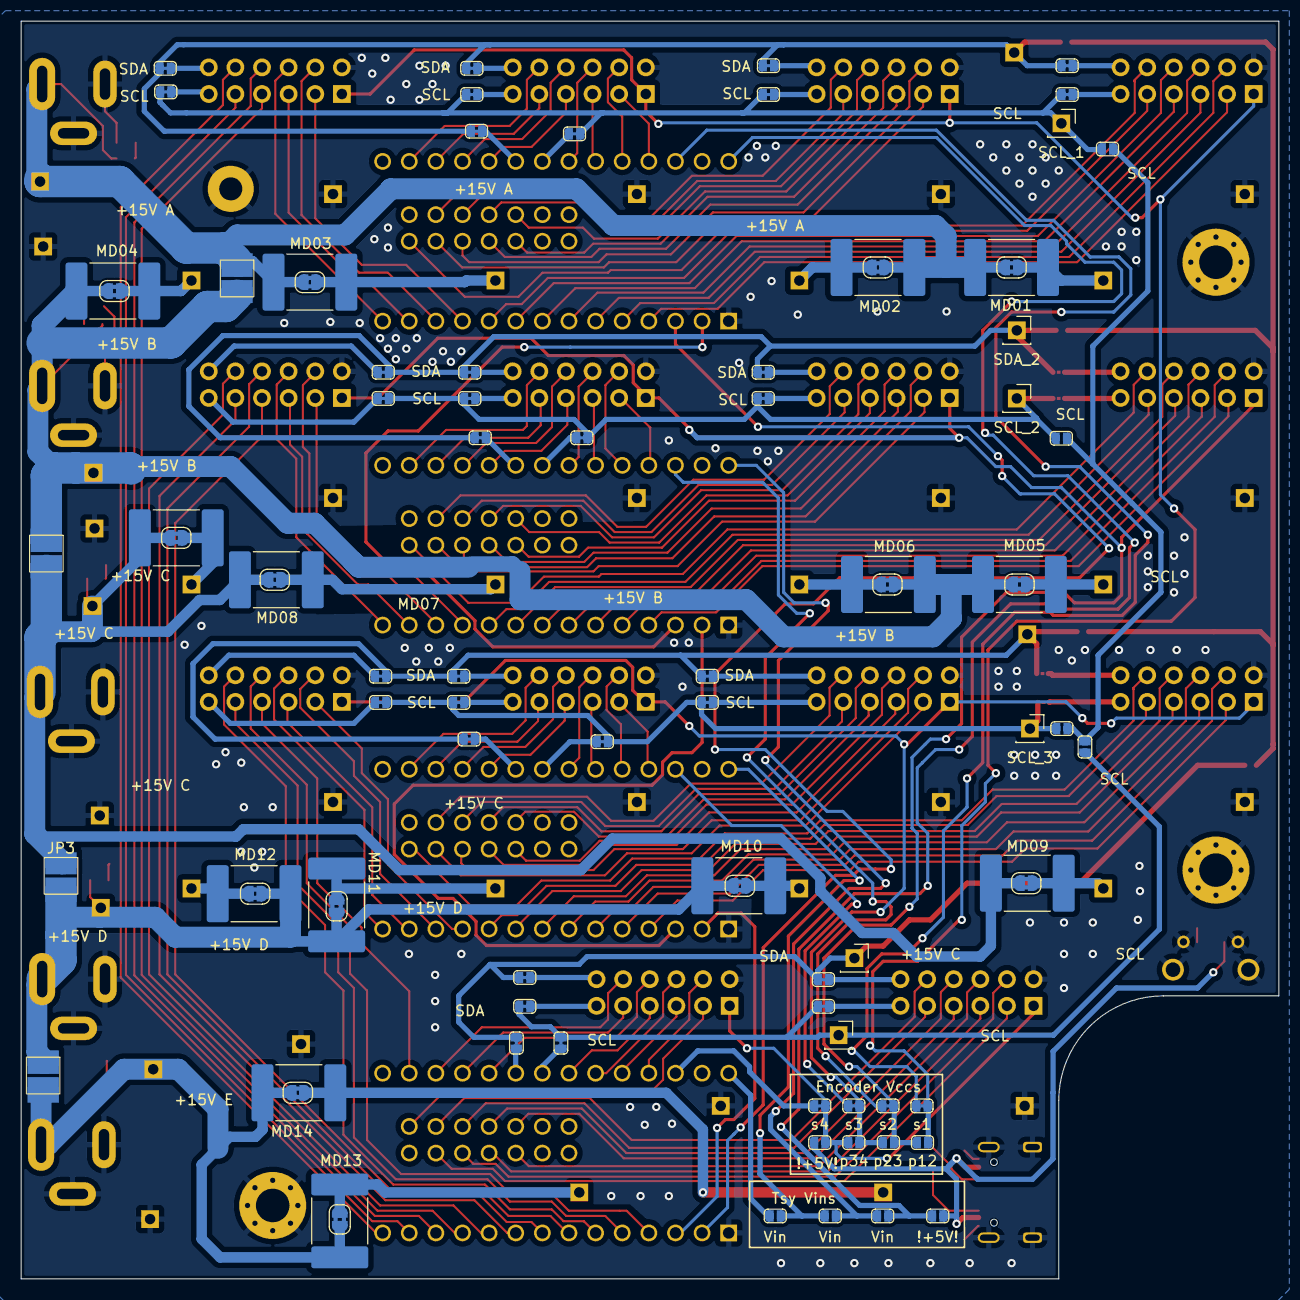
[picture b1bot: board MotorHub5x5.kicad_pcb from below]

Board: 2 copper layers, 120.0 x 120.0 mm, 147 parts (86 on the bottom side), 202 nets.

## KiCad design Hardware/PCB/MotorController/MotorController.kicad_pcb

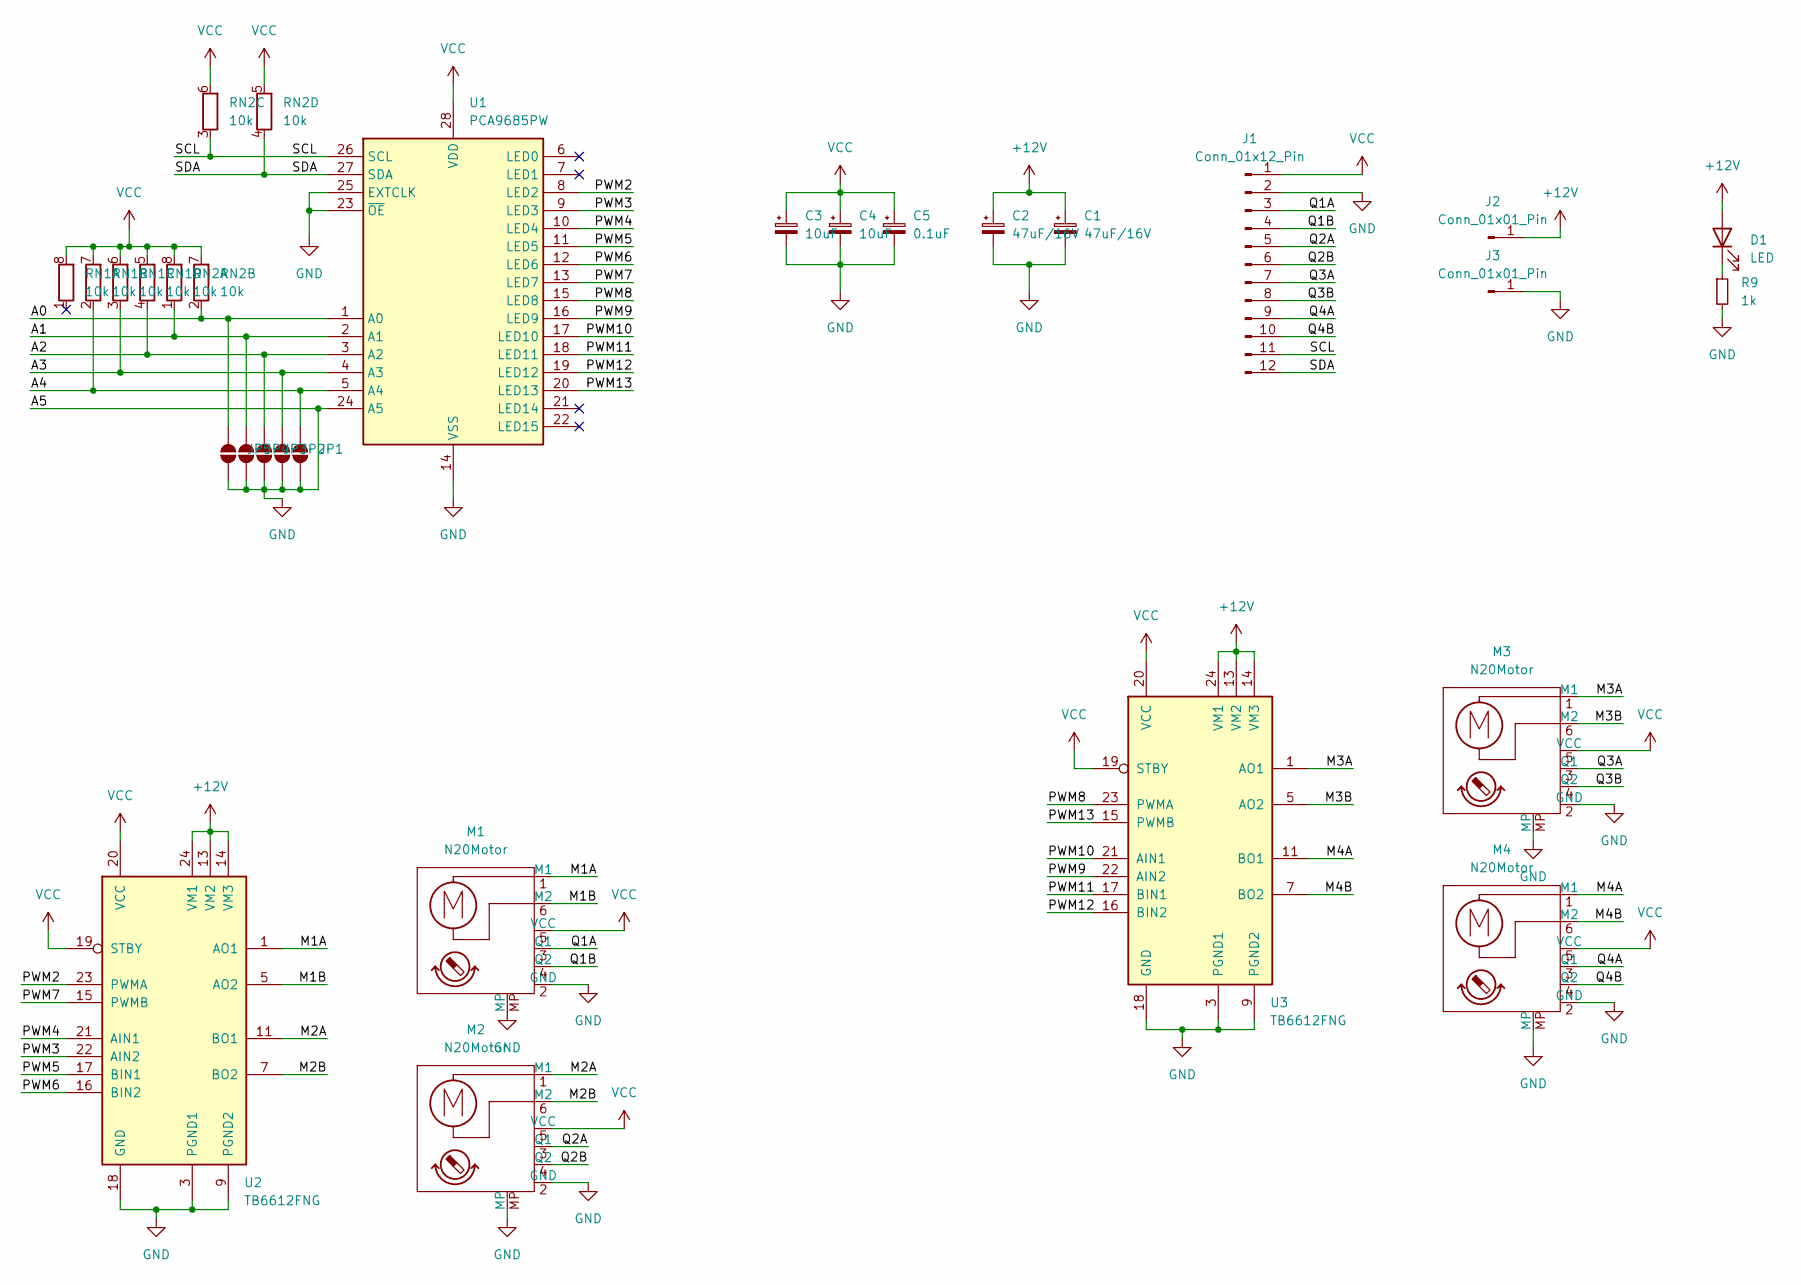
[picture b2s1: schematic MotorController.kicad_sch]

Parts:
C1, C2: 47uF/16V; CP_Elec_6.3x5.4
C3, C4: 10uF; C_0603_1608Metric_Pad1.08x0.95mm_HandSolder
C5: 0.1uF; C_0603_1608Metric_Pad1.08x0.95mm_HandSolder
D1: LED; LED_0603_1608Metric_Pad1.05x0.95mm_HandSolder
J1: Conn_01x12_Pin; PinHeader_2x06_P2.54mm_Vertical_SMD; LCSC C22395610
J2, J3: Conn_01x01_Pin; PinHeader_1x01_P2.54mm_Vertical
JP1, JP2, JP3, JP4, JP5: SolderJumper-2_Open_RoundedPad
M1, M2, M3, M4: N20Motor; N20MotorConn
R9: 1k; R_0603_1608Metric_Pad0.98x0.95mm_HandSolder
RN1, RN2: 10k; R_Array_Convex_4x0603; LCSC C29718
U1: PCA9685PW; TSSOP-28_4.4x9.7mm_P0.65mm; LCSC C2678753
U2, U3: TB6612FNG; SSOP-24_5.3x8.2mm_P0.65mm; LCSC C141517

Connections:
+12V: C1.1, C2.1, D1.2 (A), J2.1, U2.13 (VM2), U2.14 (VM3), U2.24 (VM1), U3.13 (VM2), U3.14 (VM3), U3.24 (VM1)
/A0: JP5.2 (B), RN2.2 (R2.1), U1.1 (A0)
/A1: JP4.2 (B), RN2.1 (R1.1), U1.2 (A1)
/A2: JP3.2 (B), RN1.4 (R4.1), U1.3 (A2)
/A3: JP2.2 (B), RN1.3 (R3.1), U1.4 (A3)
/A4: JP1.2 (B), RN1.2 (R2.1), U1.5 (A4)
/M1A: M1.1 (M1), U2.1 (AO1), U2.2 (AO1)
/M1B: M1.6 (M2), U2.5 (AO2), U2.6 (AO2)
/M2A: M2.1 (M1), U2.11 (BO1), U2.12 (BO1)
/M2B: M2.6 (M2), U2.7 (BO2), U2.8 (BO2)
/M3A: M3.1 (M1), U3.1 (AO1), U3.2 (AO1)
/M3B: M3.6 (M2), U3.5 (AO2), U3.6 (AO2)
/M4A: M4.1 (M1), U3.11 (BO1), U3.12 (BO1)
/M4B: M4.6 (M2), U3.7 (BO2), U3.8 (BO2)
/PWM2: U1.8 (LED2), U2.23 (PWMA)
/PWM3: U1.9 (LED3), U2.22 (AIN2)
/PWM4: U1.10 (LED4), U2.21 (AIN1)
/PWM5: U1.11 (LED5), U2.17 (BIN1)
/PWM6: U1.12 (LED6), U2.16 (BIN2)
/PWM7: U1.13 (LED7), U2.15 (PWMB)
/PWM8: U1.15 (LED8), U3.23 (PWMA)
/PWM9: U1.16 (LED9), U3.22 (AIN2)
/PWM10: U1.17 (LED10), U3.21 (AIN1)
/PWM11: U1.18 (LED11), U3.17 (BIN1)
/PWM12: U1.19 (LED12), U3.16 (BIN2)
/PWM13: U1.20 (LED13), U3.15 (PWMB)
/Q1A: J1.3, M1.3 (Q1)
/Q1B: J1.4, M1.4 (Q2)
/Q2A: J1.5, M2.3 (Q1)
/Q2B: J1.6, M2.4 (Q2)
/Q3A: J1.7, M3.3 (Q1)
/Q3B: J1.8, M3.4 (Q2)
/Q4A: J1.9, M4.3 (Q1)
/Q4B: J1.10, M4.4 (Q2)
/SCL: J1.11, RN2.3 (R3.1), U1.26 (SCL)
/SDA: J1.12, RN2.4 (R4.1), U1.27 (SDA)
GND: C1.2, C2.2, C3.2, C4.2, C5.2, J1.2, J3.1, JP1.1 (A), JP2.1 (A), JP3.1 (A), JP4.1 (A), JP5.1 (A), M1.2 (GND), M1.MP, M2.2 (GND), M2.MP, M3.2 (GND), M3.MP, M4.2 (GND), M4.MP, R9.2, U1.14 (VSS), U1.23 (~OE), U1.24 (A5), U1.25 (EXTCLK), U2.3 (PGND1), U2.4 (PGND1), U2.9 (PGND2), U2.10 (PGND2), U2.18 (GND), U3.3 (PGND1), U3.4 (PGND1), U3.9 (PGND2), U3.10 (PGND2), U3.18 (GND)
unnamed: D1.1 (K), R9.1
VCC: C3.1, C4.1, C5.1, J1.1, M1.5 (VCC), M2.5 (VCC), M3.5 (VCC), M4.5 (VCC), RN1.5 (R4.2), RN1.6 (R3.2), RN1.7 (R2.2), RN1.8 (R1.2), RN2.5 (R4.2), RN2.6 (R3.2), RN2.7 (R2.2), RN2.8 (R1.2), U1.28 (VDD), U2.19 (STBY), U2.20 (VCC), U3.19 (STBY), U3.20 (VCC)
